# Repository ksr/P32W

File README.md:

# P32W

P32W: a 32-bit homebrew computer and its operating system. Discrete
74-series logic, GALs, SRAM and flash on **9U × 340 mm cards** with three
96-pin bus connectors, on a 10-slot backplane, with the ALU in an FPGA
module (a Tang Nano 20K in sockets: every part is through-hole). A custom
minimal load/store ISA with traps, interrupts and virtual memory, and
**P32W Unix**, a multi-user V6-style Unix in C, with a native C compiler,
assembler and linker, MicroPython, Lua, SQL, BASIC and networking.

The cards: **CPU**, **MMU / data**, **memory** (1–4 × 16 MiB), **disk**
(2 CompactFlash + 2 IDE), **I/O** (4 serial ports, timer, clock, 2 USB,
Ethernet and Wi-Fi), **video** (VGA text and graphics, PS/2 keyboard and
mouse) and **debug**. They meet on a synchronous system bus that carries
physical memory cycles; the CPU and the MMU / data card have a private
local link besides.

**Start here:** [docs/architecture.md](docs/architecture.md) (the machine,
the cards, the address map) and
[docs/programmers-guide.md](docs/programmers-guide.md) (how to program it).

- Design decisions: [docs/decisions.md](docs/decisions.md)
- The operating system: [docs/os-design.md](docs/os-design.md); using P32W Unix: [docs/unix.md](docs/unix.md)
- Working from a web browser, in a GitHub codespace: [.devcontainer/README.md](.devcontainer/README.md)
- The debugger, in a browser tab (the screen, the console, the code, the CPU's insides): [tools/p32dbg/README.md](tools/p32dbg/README.md)
- The backlog: [docs/backlog.md](docs/backlog.md)
- Instruction set: [docs/isa-v0.md](docs/isa-v0.md); traps, privilege,
  interrupts, timer and virtual memory (stages A–C):
  [docs/isa-system.md](docs/isa-system.md); every instruction in one table:
  [docs/instruction-reference.md](docs/instruction-reference.md) (generated)
- Microarchitecture: [docs/microarch.md](docs/microarch.md); the CPU card: [docs/cpu-card.md](docs/cpu-card.md); the MMU / data card: [docs/mmu-card.md](docs/mmu-card.md); the memory card: [docs/mem-card.md](docs/mem-card.md); the I/O card: [docs/io-card.md](docs/io-card.md); the disk card: [docs/disk-card.md](docs/disk-card.md); the video card: [docs/video-card-acrtc.md](docs/video-card-acrtc.md) (revision 2, an HD63484 ACRTC; revision 0, never built: [docs/video-card.md](docs/video-card.md)); the debug card: [docs/debug-card.md](docs/debug-card.md); each card's theory of operation beside it (`*-card-theory.md`); how it boots: [docs/boot.md](docs/boot.md); the kernel: [docs/kernel.md](docs/kernel.md); the filesystem: [docs/filesystem.md](docs/filesystem.md). `python3 tools/mkpdf.py` makes them PDF books (docs/pdf). The GALs' fuse files and how to program every chip (TL866II+ / T48): [hardware/gal/README.md](hardware/gal/README.md)
- ISA additions measured for the new datapath: [docs/isa-measurements.md](docs/isa-measurements.md)
- The backplane bus: [docs/bus.md](docs/bus.md) (generated by `generators/p32bus.py`); the backplane itself: [docs/backplane.md](docs/backplane.md); the power budget: [docs/power-budget.md](docs/power-budget.md); timing: [docs/timing.md](docs/timing.md)
- A bench tool for any system on 96-pin DIN 41612 connectors, the shorts tester: [docs/din96-tester.md](docs/din96-tester.md) (`hardware/din96-tester/`)
- The emulators: [docs/emulators.md](docs/emulators.md)

## The cards

Every card's netlist is designed and every board routed; none is ordered
yet. The first order is the backplane, the debug card, the memory card and
the DIN 96 tester ([docs/backlog.md](docs/backlog.md)). Each card's
schematic and placement PDFs, gerbers and renders are in
`hardware/<card>/kicad/`; the emulators model the cards
(`emulator/p32io.h`, `emulator/p32uemu.c`).

## Layout

| Directory | Contents |
|---|---|
| `microcode/` | `p32isa.py` — the opcode table, single source of truth for the ISA; `p32ucode.py` — the microcode generator |
| `generators/` | `p32bus.py` — the bus (`pinnet()`, `busnet()`); `p32net.py` — device library, netlist helpers, electrical checks; `p32cards.py` — the card list; `p32gal.py` — GAL equations, exhaustive checks, a logic minimiser; `p32sim.py` — netlist-level simulator; `p32schem.py` — schematic PDFs; `p32kicad_sch.py` — KiCad schematic projects; `p32kicad_pcb.py` + `build_board.sh` + `kicad_tools.py` — place, autoroute (Freerouting 2.5) and finish boards; `gen_footprints.py` — the project's footprints (`hardware/lib`); `gen_p32opc.py`, `gen_isaref.py` — the emulator header and the instruction reference |
| `assembler/` | `p32asm.py` — two-pass assembler, linker, archiver |
| `cc/` | `p32cc.py` — the C compiler |
| `emulator/` | `p32emu.c` — instruction-level reference emulator; `p32uemu.c` — microcode-level emulator, cross-checked against it; `p32io.h` — the devices, shared by both; tests in `test/` |
| `kernel/` | P32W Unix |
| `software/` | the boot ROM monitor, libc, the commands, MicroPython, Lua, SQL, the tests ([software/README.md](software/README.md)) |
| `fpga/alu/` | the ALU in Verilog, its testbench and vector generator |
| `hardware/` | one folder per card (`<card>/kicad/`: the KiCad project, schematic and placement PDFs, gerbers, renders, `pcb-check.ini`); `gal/` the GAL JEDEC files; `lib/` the project's KiCad footprints (generated) |
| `video/` | the video cards' font images |
| `tools/` | host tools: the PDF books (`mkpdf.py`), the debugger (`p32dbg`), the terminal, the file-system tool, profilers, Kermit |
| `website/` | the project website ([website/README.md](website/README.md)) |
| `docs/` | design documents |

## Build and test

```sh
cd generators && npm install      # once: elkjs, for the wired KiCad schematic sheets
cd emulator && make test          # everything: emulators, microcode, P32W Unix
```

Assemble and run a program:

```sh
python3 assembler/p32asm.py prog.asm -o prog.bin -l prog.lst
emulator/p32emu [-t] [-l N] [-d disk.img] prog.bin
```

Tools used: Python 3, a C compiler, KiCad 10 (schematics and boards),
Freerouting 2.5 on Java 25 (`~/freerouting/`), Icarus Verilog (the ALU test).

## Licence

P32W is © 2026 Ken Rother.

- **The designs and documents** — `hardware/`, `docs/`, the manual pages (`software/man/`) and the website text:
  [CC BY 4.0](LICENSE-CC-BY-4.0.md). Share and adapt them freely, with credit.
- **The software** — everything else written for P32W: the [MIT licence](LICENSE).
- **Third-party code** keeps its own licence and notices:
  - [MicroPython](software/micropython/) (MIT, `software/micropython/LICENSE`);
  - [Lua](software/lua/) (MIT, the notice at the end of `software/lua/lua.h`);
  - `software/libc/erf.c` and `gamma.c`, from musl via MicroPython (MIT, the notice in each file).

The network tests make their own TLS test certificate on first use (`emulator/test/net_peer.py`, `tls_cert()`);
it is for "localhost" only and not a secret, so it is not kept in the repository.

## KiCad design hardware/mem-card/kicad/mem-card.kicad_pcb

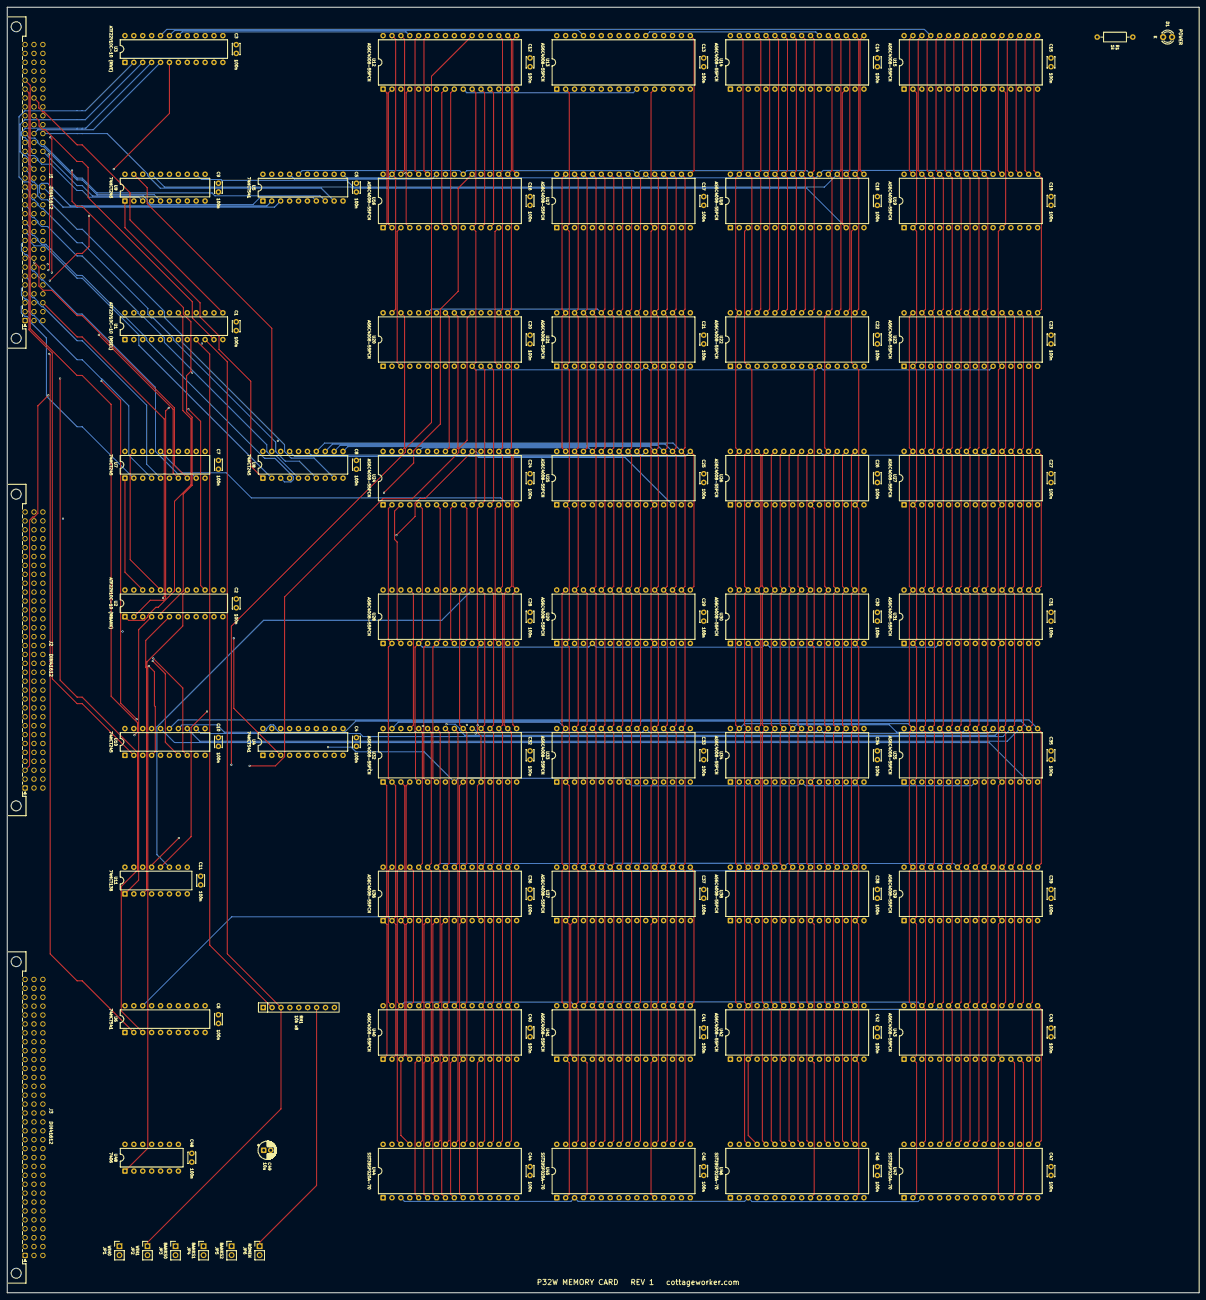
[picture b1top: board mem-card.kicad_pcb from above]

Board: 6 copper layers, 340.0 x 366.7 mm, 109 parts (0 on the bottom side), 151 nets.

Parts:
C1, C2, C3, C4, C5, C6, C7, C8, C9, C10, C11, C12, C13, C14, C15, C16, C17, C18, C19, C20, C21, C22, C23, C24, C25, C26, C27, C28, C29, C30, C31, C32, C33, C34, C35, C36, C37, C38, C39, C40, C41, C42, C43, C44, C45, C46, C47, C48: 100nF; C_Disc_D3.0mm_W2.0mm_P2.50mm
C49: 10uF 16V; CP_Radial_D5.0mm_P2.00mm
D1: LED 3mm green; LED_D3.0mm
J1, J2, J3: DIN 41612 96-pin male, right angle; DIN41612_C_3x32_Male_Horizontal_THT
JP1, JP2, JP3, JP4, JP5, JP6: jumper; PinHeader_1x02_P2.54mm_Vertical
R1: 1k; R_Axial_DIN0207_L6.3mm_D2.5mm_P10.16mm_Horizontal
RN1: 10k x 8 bussed; R_Array_SIP9
U1: ATF22V10C-10 (MSEL); DIP-24_W7.62mm
U2: ATF22V10C-10 (MBANK); DIP-24_W7.62mm
U3: ATF22V10C-10 (MWE); DIP-24_W7.62mm
U4, U5, U6: 74HCT541; DIP-20_W7.62mm
U7, U8, U9, U10: 74HCT245; DIP-20_W7.62mm
U11: 74HCT138; DIP-16_W7.62mm
U12, U13, U14, U15, U16, U17, U18, U19, U20, U21, U22, U23, U24, U25, U26, U27, U28, U29, U30, U31, U32, U33, U34, U35, U36, U37, U38, U39, U40, U41, U42, U43: AS6C4008-55PCN; DIP-32_W15.24mm
U44, U45, U46, U47: SST39SF020A-70; DIP-32_W15.24mm
U48: 7406; DIP-14_W7.62mm

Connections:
-ACK: J1.b28, U48.2
-MRD: J1.b24, U1.11
-MWR: J1.b26, U1.13
A2: J1.c7, U4.2
A3: J1.c8, U4.3
A4: J1.c9, U4.4
A5: J1.c10, U4.5
A6: J1.c11, U4.6
A7: J1.c12, U4.7
A8: J1.c13, U4.8
A9: J1.c14, U4.9
A10: J1.c15, U5.2
A11: J1.c16, U5.3
A12: J1.c17, U5.4
A13: J1.c18, U5.5
A14: J1.c19, U5.6
A15: J1.c20, U5.7
A16: J1.c21, U5.8
A17: J1.c22, U5.9
A18: J1.c23, U6.2
A19: J1.c24, U6.3
A20: J1.c25, U2.3, U6.4
A21: J1.c26, U2.4, U11.1
A22: J1.c27, U2.5, U11.2
A23: J1.c28, U2.6, U11.3
A24: J1.c29, U1.1
A25: J1.c30, U1.2
A26: J1.b4, U1.3
A27: J1.b6, U1.4
A28: J1.b8, U1.5
A29: J1.b10, U1.6
A30: J1.b12, U1.7
A31: J1.b14, U1.8
ACK: U2.17, U48.1
BANK0_N: U11.15, U12.22, U13.22, U14.22, U15.22
BANK1_N: U11.14, U16.22, U17.22, U18.22, U19.22
BANK2_N: U11.13, U20.22, U21.22, U22.22, U23.22
BANK3_N: U11.12, U24.22, U25.22, U26.22, U27.22
BANK4_N: U11.11, U28.22, U29.22, U30.22, U31.22
BANK5_N: U11.10, U32.22, U33.22, U34.22, U35.22
BANK6_N: U11.9, U36.22, U37.22, U38.22, U39.22
BANK7_N: U11.7, U40.22, U41.22, U42.22, U43.22
BANKS0: JP3.1, RN1.4, U2.7
BANKS1: JP4.1, RN1.5, U2.8
BANKS2: JP5.1, RN1.6, U2.9
BE0: J1.b16, U3.2
BE1: J1.b18, U3.3
BE2: J1.b20, U3.4
BE3: J1.b22, U3.5
CARDRD: U1.18, U2.1, U3.7
CARDWR: U1.19, U2.2
CLK: J2.a3, U3.6
D0: J1.a3, U7.2
D1: J1.a4, U7.3
D2: J1.a5, U7.4
D3: J1.a6, U7.5
D4: J1.a7, U7.6
D5: J1.a8, U7.7
D6: J1.a9, U7.8
D7: J1.a10, U7.9
D8: J1.a11, U8.2
D9: J1.a12, U8.3
D10: J1.a13, U8.4
D11: J1.a14, U8.5
D12: J1.a15, U8.6
D13: J1.a16, U8.7
D14: J1.a17, U8.8
D15: J1.a18, U8.9
D16: J1.a19, U9.2
D17: J1.a20, U9.3
D18: J1.a21, U9.4
D19: J1.a22, U9.5
D20: J1.a23, U9.6
D21: J1.a24, U9.7
D22: J1.a25, U9.8
D23: J1.a26, U9.9
D24: J1.a27, U10.2
D25: J1.a28, U10.3
D26: J1.a29, U10.4
D27: J1.a30, U10.5
D28: J1.c3, U10.6
D29: J1.c4, U10.7
D30: J1.c5, U10.8
D31: J1.c6, U10.9
DIRW: U2.22, U7.1, U8.1, U9.1, U10.1
GND: C1.2, C2.2, C3.2, C4.2, C5.2, C6.2, C7.2, C8.2, C9.2, C10.2, C11.2, C12.2, C13.2, C14.2, C15.2, C16.2, C17.2, C18.2, C19.2, C20.2, C21.2, C22.2, C23.2, C24.2, C25.2, C26.2, C27.2, C28.2, C29.2, C30.2, C31.2, C32.2, C33.2, C34.2, C35.2, C36.2, C37.2, C38.2, C39.2, C40.2, C41.2, C42.2, C43.2, C44.2, C45.2, C46.2, C47.2, C48.2, C49.2, D1.1, J1.a31, J1.a32, J1.b3, J1.b5, J1.b7, J1.b9, J1.b11, J1.b13, J1.b15, J1.b17, J1.b19, J1.b21, J1.b23, J1.b25, J1.b27, J1.b29, J1.b31, J1.b32, J1.c31, J1.c32, J2.a31, J2.a32, J2.b3, J2.b5, J2.b7, J2.b9, J2.b11, J2.b13, J2.b15, J2.b17, J2.b19, J2.b21, J2.b23, J2.b25, J2.b27, J2.b29, J2.b31, J2.b32, J2.c31, J2.c32, J3.a31, J3.a32, J3.b3, J3.b5, J3.b7, J3.b9, J3.b11, J3.b13, J3.b15, J3.b17, J3.b19, J3.b21, J3.b23, J3.b25, J3.b27, J3.b29, J3.b31, J3.b32, J3.c31, J3.c32, JP1.2, JP2.2, JP3.2, JP4.2, JP5.2, JP6.2, U1.12, U2.12, U3.12, U4.1, U4.10, U4.19, U5.1, U5.10, U5.19, U6.1, U6.5, U6.6, U6.7, U6.8, U6.9, U6.10, U6.19, U7.10, U8.10, U9.10, U10.10, U11.5, U11.8, U12.16, U13.16, U14.16, U15.16, U16.16, U17.16, U18.16, U19.16, U20.16, U21.16, U22.16, U23.16, U24.16, U25.16, U26.16, U27.16, U28.16, U29.16, U30.16, U31.16, U32.16, U33.16, U34.16, U35.16, U36.16, U37.16, U38.16, U39.16, U40.16, U41.16, U42.16, U43.16, U44.16, U45.16, U46.16, U47.16, U48.3, U48.5, U48.7, U48.9, U48.11, U48.13
MA0: U4.18, U12.12, U13.12, U14.12, U15.12, U16.12, U17.12, U18.12, U19.12, U20.12, U21.12, U22.12, U23.12, U24.12, U25.12, U26.12, U27.12, U28.12, U29.12, U30.12, U31.12, U32.12, U33.12, U34.12, U35.12, U36.12, U37.12, U38.12, U39.12, U40.12, U41.12, U42.12, U43.12, U44.12, U45.12, U46.12, U47.12
MA1: U4.17, U12.11, U13.11, U14.11, U15.11, U16.11, U17.11, U18.11, U19.11, U20.11, U21.11, U22.11, U23.11, U24.11, U25.11, U26.11, U27.11, U28.11, U29.11, U30.11, U31.11, U32.11, U33.11, U34.11, U35.11, U36.11, U37.11, U38.11, U39.11, U40.11, U41.11, U42.11, U43.11, U44.11, U45.11, U46.11, U47.11
MA2: U4.16, U12.10, U13.10, U14.10, U15.10, U16.10, U17.10, U18.10, U19.10, U20.10, U21.10, U22.10, U23.10, U24.10, U25.10, U26.10, U27.10, U28.10, U29.10, U30.10, U31.10, U32.10, U33.10, U34.10, U35.10, U36.10, U37.10, U38.10, U39.10, U40.10, U41.10, U42.10, U43.10, U44.10, U45.10, U46.10, U47.10
MA3: U4.15, U12.9, U13.9, U14.9, U15.9, U16.9, U17.9, U18.9, U19.9, U20.9, U21.9, U22.9, U23.9, U24.9, U25.9, U26.9, U27.9, U28.9, U29.9, U30.9, U31.9, U32.9, U33.9, U34.9, U35.9, U36.9, U37.9, U38.9, U39.9, U40.9, U41.9, U42.9, U43.9, U44.9, U45.9, U46.9, U47.9
MA4: U4.14, U12.8, U13.8, U14.8, U15.8, U16.8, U17.8, U18.8, U19.8, U20.8, U21.8, U22.8, U23.8, U24.8, U25.8, U26.8, U27.8, U28.8, U29.8, U30.8, U31.8, U32.8, U33.8, U34.8, U35.8, U36.8, U37.8, U38.8, U39.8, U40.8, U41.8, U42.8, U43.8, U44.8, U45.8, U46.8, U47.8
MA5: U4.13, U12.7, U13.7, U14.7, U15.7, U16.7, U17.7, U18.7, U19.7, U20.7, U21.7, U22.7, U23.7, U24.7, U25.7, U26.7, U27.7, U28.7, U29.7, U30.7, U31.7, U32.7, U33.7, U34.7, U35.7, U36.7, U37.7, U38.7, U39.7, U40.7, U41.7, U42.7, U43.7, U44.7, U45.7, U46.7, U47.7
MA6: U4.12, U12.6, U13.6, U14.6, U15.6, U16.6, U17.6, U18.6, U19.6, U20.6, U21.6, U22.6, U23.6, U24.6, U25.6, U26.6, U27.6, U28.6, U29.6, U30.6, U31.6, U32.6, U33.6, U34.6, U35.6, U36.6, U37.6, U38.6, U39.6, U40.6, U41.6, U42.6, U43.6, U44.6, U45.6, U46.6, U47.6
MA7: U4.11, U12.5, U13.5, U14.5, U15.5, U16.5, U17.5, U18.5, U19.5, U20.5, U21.5, U22.5, U23.5, U24.5, U25.5, U26.5, U27.5, U28.5, U29.5, U30.5, U31.5, U32.5, U33.5, U34.5, U35.5, U36.5, U37.5, U38.5, U39.5, U40.5, U41.5, U42.5, U43.5, U44.5, U45.5, U46.5, U47.5
MA8: U5.18, U12.27, U13.27, U14.27, U15.27, U16.27, U17.27, U18.27, U19.27, U20.27, U21.27, U22.27, U23.27, U24.27, U25.27, U26.27, U27.27, U28.27, U29.27, U30.27, U31.27, U32.27, U33.27, U34.27, U35.27, U36.27, U37.27, U38.27, U39.27, U40.27, U41.27, U42.27, U43.27, U44.27, U45.27, U46.27, U47.27
MA9: U5.17, U12.26, U13.26, U14.26, U15.26, U16.26, U17.26, U18.26, U19.26, U20.26, U21.26, U22.26, U23.26, U24.26, U25.26, U26.26, U27.26, U28.26, U29.26, U30.26, U31.26, U32.26, U33.26, U34.26, U35.26, U36.26, U37.26, U38.26, U39.26, U40.26, U41.26, U42.26, U43.26, U44.26, U45.26, U46.26, U47.26
MA10: U5.16, U12.23, U13.23, U14.23, U15.23, U16.23, U17.23, U18.23, U19.23, U20.23, U21.23, U22.23, U23.23, U24.23, U25.23, U26.23, U27.23, U28.23, U29.23, U30.23, U31.23, U32.23, U33.23, U34.23, U35.23, U36.23, U37.23, U38.23, U39.23, U40.23, U41.23, U42.23, U43.23, U44.23, U45.23, U46.23, U47.23
MA11: U5.15, U12.25, U13.25, U14.25, U15.25, U16.25, U17.25, U18.25, U19.25, U20.25, U21.25, U22.25, U23.25, U24.25, U25.25, U26.25, U27.25, U28.25, U29.25, U30.25, U31.25, U32.25, U33.25, U34.25, U35.25, U36.25, U37.25, U38.25, U39.25, U40.25, U41.25, U42.25, U43.25, U44.25, U45.25, U46.25, U47.25
MA12: U5.14, U12.4, U13.4, U14.4, U15.4, U16.4, U17.4, U18.4, U19.4, U20.4, U21.4, U22.4, U23.4, U24.4, U25.4, U26.4, U27.4, U28.4, U29.4, U30.4, U31.4, U32.4, U33.4, U34.4, U35.4, U36.4, U37.4, U38.4, U39.4, U40.4, U41.4, U42.4, U43.4, U44.4, U45.4, U46.4, U47.4
MA13: U5.13, U12.28, U13.28, U14.28, U15.28, U16.28, U17.28, U18.28, U19.28, U20.28, U21.28, U22.28, U23.28, U24.28, U25.28, U26.28, U27.28, U28.28, U29.28, U30.28, U31.28, U32.28, U33.28, U34.28, U35.28, U36.28, U37.28, U38.28, U39.28, U40.28, U41.28, U42.28, U43.28, U44.28, U45.28, U46.28, U47.28
MA14: U5.12, U12.3, U13.3, U14.3, U15.3, U16.3, U17.3, U18.3, U19.3, U20.3, U21.3, U22.3, U23.3, U24.3, U25.3, U26.3, U27.3, U28.3, U29.3, U30.3, U31.3, U32.3, U33.3, U34.3, U35.3, U36.3, U37.3, U38.3, U39.3, U40.3, U41.3, U42.3, U43.3, U44.29, U45.29, U46.29, U47.29
MA15: U5.11, U12.31, U13.31, U14.31, U15.31, U16.31, U17.31, U18.31, U19.31, U20.31, U21.31, U22.31, U23.31, U24.31, U25.31, U26.31, U27.31, U28.31, U29.31, U30.31, U31.31, U32.31, U33.31, U34.31, U35.31, U36.31, U37.31, U38.31, U39.31, U40.31, U41.31, U42.31, U43.31, U44.3, U45.3, U46.3, U47.3
MA16: U6.18, U12.2, U13.2, U14.2, U15.2, U16.2, U17.2, U18.2, U19.2, U20.2, U21.2, U22.2, U23.2, U24.2, U25.2, U26.2, U27.2, U28.2, U29.2, U30.2, U31.2, U32.2, U33.2, U34.2, U35.2, U36.2, U37.2, U38.2, U39.2, U40.2, U41.2, U42.2, U43.2, U44.2, U45.2, U46.2, U47.2
MA17: U6.17, U12.30, U13.30, U14.30, U15.30, U16.30, U17.30, U18.30, U19.30, U20.30, U21.30, U22.30, U23.30, U24.30, U25.30, U26.30, U27.30, U28.30, U29.30, U30.30, U31.30, U32.30, U33.30, U34.30, U35.30, U36.30, U37.30, U38.30, U39.30, U40.30, U41.30, U42.30, U43.30, U44.30, U45.30, U46.30, U47.30
MA18: U6.16, U12.1, U13.1, U14.1, U15.1, U16.1, U17.1, U18.1, U19.1, U20.1, U21.1, U22.1, U23.1, U24.1, U25.1, U26.1, U27.1, U28.1, U29.1, U30.1, U31.1, U32.1, U33.1, U34.1, U35.1, U36.1, U37.1, U38.1, U39.1, U40.1, U41.1, U42.1, U43.1
MD0: U7.18, U12.13, U16.13, U20.13, U24.13, U28.13, U32.13, U36.13, U40.13, U44.13
MD1: U7.17, U12.14, U16.14, U20.14, U24.14, U28.14, U32.14, U36.14, U40.14, U44.14
MD2: U7.16, U12.15, U16.15, U20.15, U24.15, U28.15, U32.15, U36.15, U40.15, U44.15
MD3: U7.15, U12.17, U16.17, U20.17, U24.17, U28.17, U32.17, U36.17, U40.17, U44.17
MD4: U7.14, U12.18, U16.18, U20.18, U24.18, U28.18, U32.18, U36.18, U40.18, U44.18
MD5: U7.13, U12.19, U16.19, U20.19, U24.19, U28.19, U32.19, U36.19, U40.19, U44.19
MD6: U7.12, U12.20, U16.20, U20.20, U24.20, U28.20, U32.20, U36.20, U40.20, U44.20
MD7: U7.11, U12.21, U16.21, U20.21, U24.21, U28.21, U32.21, U36.21, U40.21, U44.21
MD8: U8.18, U13.13, U17.13, U21.13, U25.13, U29.13, U33.13, U37.13, U41.13, U45.13
MD9: U8.17, U13.14, U17.14, U21.14, U25.14, U29.14, U33.14, U37.14, U41.14, U45.14
MD10: U8.16, U13.15, U17.15, U21.15, U25.15, U29.15, U33.15, U37.15, U41.15, U45.15
MD11: U8.15, U13.17, U17.17, U21.17, U25.17, U29.17, U33.17, U37.17, U41.17, U45.17
MD12: U8.14, U13.18, U17.18, U21.18, U25.18, U29.18, U33.18, U37.18, U41.18, U45.18
MD13: U8.13, U13.19, U17.19, U21.19, U25.19, U29.19, U33.19, U37.19, U41.19, U45.19
MD14: U8.12, U13.20, U17.20, U21.20, U25.20, U29.20, U33.20, U37.20, U41.20, U45.20
MD15: U8.11, U13.21, U17.21, U21.21, U25.21, U29.21, U33.21, U37.21, U41.21, U45.21
MD16: U9.18, U14.13, U18.13, U22.13, U26.13, U30.13, U34.13, U38.13, U42.13, U46.13
MD17: U9.17, U14.14, U18.14, U22.14, U26.14, U30.14, U34.14, U38.14, U42.14, U46.14
MD18: U9.16, U14.15, U18.15, U22.15, U26.15, U30.15, U34.15, U38.15, U42.15, U46.15
MD19: U9.15, U14.17, U18.17, U22.17, U26.17, U30.17, U34.17, U38.17, U42.17, U46.17
MD20: U9.14, U14.18, U18.18, U22.18, U26.18, U30.18, U34.18, U38.18, U42.18, U46.18
MD21: U9.13, U14.19, U18.19, U22.19, U26.19, U30.19, U34.19, U38.19, U42.19, U46.19
MD22: U9.12, U14.20, U18.20, U22.20, U26.20, U30.20, U34.20, U38.20, U42.20, U46.20
MD23: U9.11, U14.21, U18.21, U22.21, U26.21, U30.21, U34.21, U38.21, U42.21, U46.21
MD24: U10.18, U15.13, U19.13, U23.13, U27.13, U31.13, U35.13, U39.13, U43.13, U47.13
MD25: U10.17, U15.14, U19.14, U23.14, U27.14, U31.14, U35.14, U39.14, U43.14, U47.14
MD26: U10.16, U15.15, U19.15, U23.15, U27.15, U31.15, U35.15, U39.15, U43.15, U47.15
MD27: U10.15, U15.17, U19.17, U23.17, U27.17, U31.17, U35.17, U39.17, U43.17, U47.17
MD28: U10.14, U15.18, U19.18, U23.18, U27.18, U31.18, U35.18, U39.18, U43.18, U47.18
MD29: U10.13, U15.19, U19.19, U23.19, U27.19, U31.19, U35.19, U39.19, U43.19, U47.19
MD30: U10.12, U15.20, U19.20, U23.20, U27.20, U31.20, U35.20, U39.20, U43.20, U47.20
MD31: U10.11, U15.21, U19.21, U23.21, U27.21, U31.21, U35.21, U39.21, U43.21, U47.21
PWRLED_A: D1.2, R1.2
RAMENN: U2.19, U11.4
RAMWR: U2.15, U3.1
RDOEN: U3.16, U12.24, U13.24, U14.24, U15.24, U16.24, U17.24, U18.24, U19.24, U20.24, U21.24, U22.24, U23.24, U24.24, U25.24, U26.24, U27.24, U28.24, U29.24, U30.24, U31.24, U32.24, U33.24, U34.24, U35.24, U36.24, U37.24, U38.24, U39.24, U40.24, U41.24, U42.24, U43.24, U44.24, U45.24, U46.24, U47.24
ROMCSN: U2.16, U44.22, U45.22, U46.22, U47.22
ROMEN: JP6.1, RN1.7, U2.10
VCC: C1.1, C2.1, C3.1, C4.1, C5.1, C6.1, C7.1, C8.1, C9.1, C10.1, C11.1, C12.1, C13.1, C14.1, C15.1, C16.1, C17.1, C18.1, C19.1, C20.1, C21.1, C22.1, C23.1, C24.1, C25.1, C26.1, C27.1, C28.1, C29.1, C30.1, C31.1, C32.1, C33.1, C34.1, C35.1, C36.1, C37.1, C38.1, C39.1, C40.1, C41.1, C42.1, C43.1, C44.1, C45.1, C46.1, C47.1, C48.1, C49.1, J1.a1, J1.a2, J1.b1, J1.b2, J1.c1, J1.c2, J2.a1, J2.a2, J2.b1, J2.b2, J2.b4, J2.b6, J2.b8, J2.b10, J2.b12, J2.b14, J2.b16, J2.b18, J2.b20, J2.b22, J2.b24, J2.b26, J2.b28, J2.b30, J2.c1, J2.c2, J3.a1, J3.a2, J3.b1, J3.b2, J3.c1, J3.c2, R1.1, RN1.1, U1.24, U2.24, U3.24, U4.20, U5.20, U6.20, U7.20, U8.20, U9.20, U10.20, U11.6, U11.16, U12.32, U13.32, U14.32, U15.32, U16.32, U17.32, U18.32, U19.32, U20.32, U21.32, U22.32, U23.32, U24.32, U25.32, U26.32, U27.32, U28.32, U29.32, U30.32, U31.32, U32.32, U33.32, U34.32, U35.32, U36.32, U37.32, U38.32, U39.32, U40.32, U41.32, U42.32, U43.32, U44.31, U44.32, U45.31, U45.32, U46.31, U46.32, U47.31, U47.32, U48.14
WE0N: U3.18, U12.29, U16.29, U20.29, U24.29, U28.29, U32.29, U36.29, U40.29
WE1N: U3.19, U13.29, U17.29, U21.29, U25.29, U29.29, U33.29, U37.29, U41.29
WE2N: U3.17, U14.29, U18.29, U22.29, U26.29, U30.29, U34.29, U38.29, U42.29
WE3N: U3.20, U15.29, U19.29, U23.29, U27.29, U31.29, U35.29, U39.29, U43.29
WIN0: JP1.1, RN1.2, U1.9
WIN1: JP2.1, RN1.3, U1.10
XOEN: U2.20, U7.19, U8.19, U9.19, U10.19

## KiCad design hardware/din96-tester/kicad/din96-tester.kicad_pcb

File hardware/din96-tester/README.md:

# The DIN 96 shorts tester

A bench tool for any system on 96-pin DIN 41612 connectors (P32W, YACC1): plugged onto one connector of a board
that has nothing on it yet but its connectors, it finds every pin joined to another. An Arduino Nano, six
MCP23S17 port expanders, a TEST button, an eight-lever TYPE switch, and three LEDs: POWER (yellow), PASS (green),
FAIL (red). What it is, how to use it and how it works:
[docs/din96-tester.md](../../docs/din96-tester.md) (decisions D129, and D130: its check before the order).

- `kicad/`: the schematic, the board and its order files, made by `generators/card_din96.py` (the netlist) and
  `generators/p32din96.py` (the board): `sh generators/build_schematics.sh din96-tester`, then
  `sh generators/build_board.sh din96-tester`. Generators are canon: do not edit the board by hand.
- `firmware/din96_tester/`: the Arduino sketch. `profiles.h` is written by `python3 generators/card_din96.py
  --firmware`; the other two files are edited by hand. `make test` (in `emulator/`) runs its logic on made-up
  boards (`emulator/test/din96_test.c`) and the sketch itself against a model of this board
  (`emulator/test/din96_sim.cc`).
- `pins/`: a pin table a system (`CONNECTOR PIN SIGNAL`), which the connector types are made from. `p32w.txt` is
  written from P32W's bus definition; `yacc1.txt` is a copy of what YACC1-D's `tools/bus_pins.py` prints.

Another system: put its pin table in `pins/`, add its connector to `TYPES` in `generators/card_din96.py`, run
`--firmware`, and load the sketch again.

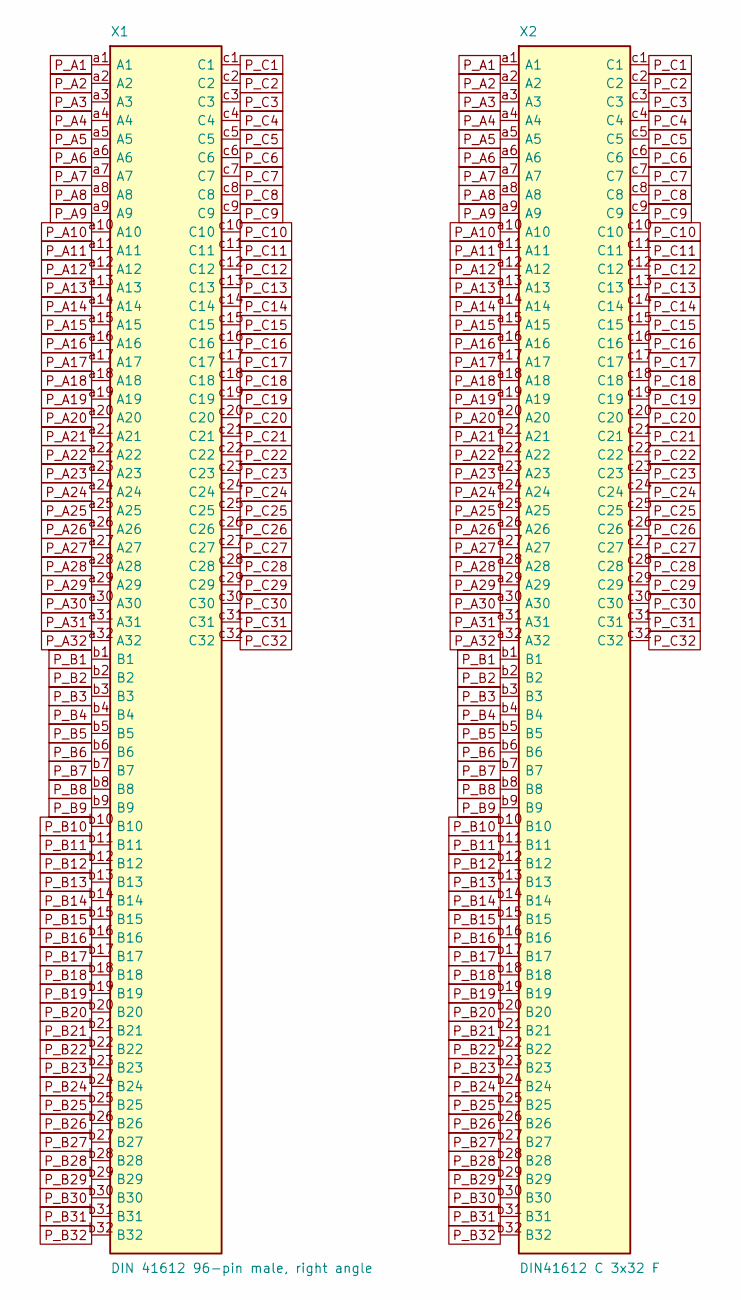
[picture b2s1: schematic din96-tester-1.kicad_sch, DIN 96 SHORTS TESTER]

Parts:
X1: DIN 41612 96-pin male, right angle; DIN41612_C_3x32_Male_Horizontal_THT
X2: DIN41612 C 3x32 F; DIN41612_C_3x32_Female_Vertical_THT

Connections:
P_A1: X1.a1 (A1), X2.a1 (A1); also elsewhere on the board
P_A2: X1.a2 (A2), X2.a2 (A2); also elsewhere on the board
P_A3: X1.a3 (A3), X2.a3 (A3); also elsewhere on the board
P_A4: X1.a4 (A4), X2.a4 (A4); also elsewhere on the board
P_A5: X1.a5 (A5), X2.a5 (A5); also elsewhere on the board
P_A6: X1.a6 (A6), X2.a6 (A6); also elsewhere on the board
P_A7: X1.a7 (A7), X2.a7 (A7); also elsewhere on the board
P_A8: X1.a8 (A8), X2.a8 (A8); also elsewhere on the board
P_A9: X1.a9 (A9), X2.a9 (A9); also elsewhere on the board
P_A10: X1.a10 (A10), X2.a10 (A10); also elsewhere on the board
P_A11: X1.a11 (A11), X2.a11 (A11); also elsewhere on the board
P_A12: X1.a12 (A12), X2.a12 (A12); also elsewhere on the board
P_A13: X1.a13 (A13), X2.a13 (A13); also elsewhere on the board
P_A14: X1.a14 (A14), X2.a14 (A14); also elsewhere on the board
P_A15: X1.a15 (A15), X2.a15 (A15); also elsewhere on the board
P_A16: X1.a16 (A16), X2.a16 (A16); also elsewhere on the board
P_A17: X1.a17 (A17), X2.a17 (A17); also elsewhere on the board
P_A18: X1.a18 (A18), X2.a18 (A18); also elsewhere on the board
P_A19: X1.a19 (A19), X2.a19 (A19); also elsewhere on the board
P_A20: X1.a20 (A20), X2.a20 (A20); also elsewhere on the board
P_A21: X1.a21 (A21), X2.a21 (A21); also elsewhere on the board
P_A22: X1.a22 (A22), X2.a22 (A22); also elsewhere on the board
P_A23: X1.a23 (A23), X2.a23 (A23); also elsewhere on the board
P_A24: X1.a24 (A24), X2.a24 (A24); also elsewhere on the board
P_A25: X1.a25 (A25), X2.a25 (A25); also elsewhere on the board
P_A26: X1.a26 (A26), X2.a26 (A26); also elsewhere on the board
P_A27: X1.a27 (A27), X2.a27 (A27); also elsewhere on the board
P_A28: X1.a28 (A28), X2.a28 (A28); also elsewhere on the board
P_A29: X1.a29 (A29), X2.a29 (A29); also elsewhere on the board
P_A30: X1.a30 (A30), X2.a30 (A30); also elsewhere on the board
P_A31: X1.a31 (A31), X2.a31 (A31); also elsewhere on the board
P_A32: X1.a32 (A32), X2.a32 (A32); also elsewhere on the board
P_B1: X1.b1 (B1), X2.b1 (B1); also elsewhere on the board
P_B2: X1.b2 (B2), X2.b2 (B2); also elsewhere on the board
P_B3: X1.b3 (B3), X2.b3 (B3); also elsewhere on the board
P_B4: X1.b4 (B4), X2.b4 (B4); also elsewhere on the board
P_B5: X1.b5 (B5), X2.b5 (B5); also elsewhere on the board
P_B6: X1.b6 (B6), X2.b6 (B6); also elsewhere on the board
P_B7: X1.b7 (B7), X2.b7 (B7); also elsewhere on the board
P_B8: X1.b8 (B8), X2.b8 (B8); also elsewhere on the board
P_B9: X1.b9 (B9), X2.b9 (B9); also elsewhere on the board
P_B10: X1.b10 (B10), X2.b10 (B10); also elsewhere on the board
P_B11: X1.b11 (B11), X2.b11 (B11); also elsewhere on the board
P_B12: X1.b12 (B12), X2.b12 (B12); also elsewhere on the board
P_B13: X1.b13 (B13), X2.b13 (B13); also elsewhere on the board
P_B14: X1.b14 (B14), X2.b14 (B14); also elsewhere on the board
P_B15: X1.b15 (B15), X2.b15 (B15); also elsewhere on the board
P_B16: X1.b16 (B16), X2.b16 (B16); also elsewhere on the board
P_B17: X1.b17 (B17), X2.b17 (B17); also elsewhere on the board
P_B18: X1.b18 (B18), X2.b18 (B18); also elsewhere on the board
P_B19: X1.b19 (B19), X2.b19 (B19); also elsewhere on the board
P_B20: X1.b20 (B20), X2.b20 (B20); also elsewhere on the board
P_B21: X1.b21 (B21), X2.b21 (B21); also elsewhere on the board
P_B22: X1.b22 (B22), X2.b22 (B22); also elsewhere on the board
P_B23: X1.b23 (B23), X2.b23 (B23); also elsewhere on the board
P_B24: X1.b24 (B24), X2.b24 (B24); also elsewhere on the board
P_B25: X1.b25 (B25), X2.b25 (B25); also elsewhere on the board
P_B26: X1.b26 (B26), X2.b26 (B26); also elsewhere on the board
P_B27: X1.b27 (B27), X2.b27 (B27); also elsewhere on the board
P_B28: X1.b28 (B28), X2.b28 (B28); also elsewhere on the board
P_B29: X1.b29 (B29), X2.b29 (B29); also elsewhere on the board
P_B30: X1.b30 (B30), X2.b30 (B30); also elsewhere on the board
P_B31: X1.b31 (B31), X2.b31 (B31); also elsewhere on the board
P_B32: X1.b32 (B32), X2.b32 (B32); also elsewhere on the board
P_C1: X1.c1 (C1), X2.c1 (C1); also elsewhere on the board
P_C2: X1.c2 (C2), X2.c2 (C2); also elsewhere on the board
P_C3: X1.c3 (C3), X2.c3 (C3); also elsewhere on the board
P_C4: X1.c4 (C4), X2.c4 (C4); also elsewhere on the board
P_C5: X1.c5 (C5), X2.c5 (C5); also elsewhere on the board
P_C6: X1.c6 (C6), X2.c6 (C6); also elsewhere on the board
P_C7: X1.c7 (C7), X2.c7 (C7); also elsewhere on the board
P_C8: X1.c8 (C8), X2.c8 (C8); also elsewhere on the board
P_C9: X1.c9 (C9), X2.c9 (C9); also elsewhere on the board
P_C10: X1.c10 (C10), X2.c10 (C10); also elsewhere on the board
P_C11: X1.c11 (C11), X2.c11 (C11); also elsewhere on the board
P_C12: X1.c12 (C12), X2.c12 (C12); also elsewhere on the board
P_C13: X1.c13 (C13), X2.c13 (C13); also elsewhere on the board
P_C14: X1.c14 (C14), X2.c14 (C14); also elsewhere on the board
P_C15: X1.c15 (C15), X2.c15 (C15); also elsewhere on the board
P_C16: X1.c16 (C16), X2.c16 (C16); also elsewhere on the board
P_C17: X1.c17 (C17), X2.c17 (C17); also elsewhere on the board
P_C18: X1.c18 (C18), X2.c18 (C18); also elsewhere on the board
P_C19: X1.c19 (C19), X2.c19 (C19); also elsewhere on the board
P_C20: X1.c20 (C20), X2.c20 (C20); also elsewhere on the board
P_C21: X1.c21 (C21), X2.c21 (C21); also elsewhere on the board
P_C22: X1.c22 (C22), X2.c22 (C22); also elsewhere on the board
P_C23: X1.c23 (C23), X2.c23 (C23); also elsewhere on the board
P_C24: X1.c24 (C24), X2.c24 (C24); also elsewhere on the board
P_C25: X1.c25 (C25), X2.c25 (C25); also elsewhere on the board
P_C26: X1.c26 (C26), X2.c26 (C26); also elsewhere on the board
P_C27: X1.c27 (C27), X2.c27 (C27); also elsewhere on the board
P_C28: X1.c28 (C28), X2.c28 (C28); also elsewhere on the board
P_C29: X1.c29 (C29), X2.c29 (C29); also elsewhere on the board
P_C30: X1.c30 (C30), X2.c30 (C30); also elsewhere on the board
P_C31: X1.c31 (C31), X2.c31 (C31); also elsewhere on the board
P_C32: X1.c32 (C32), X2.c32 (C32); also elsewhere on the board

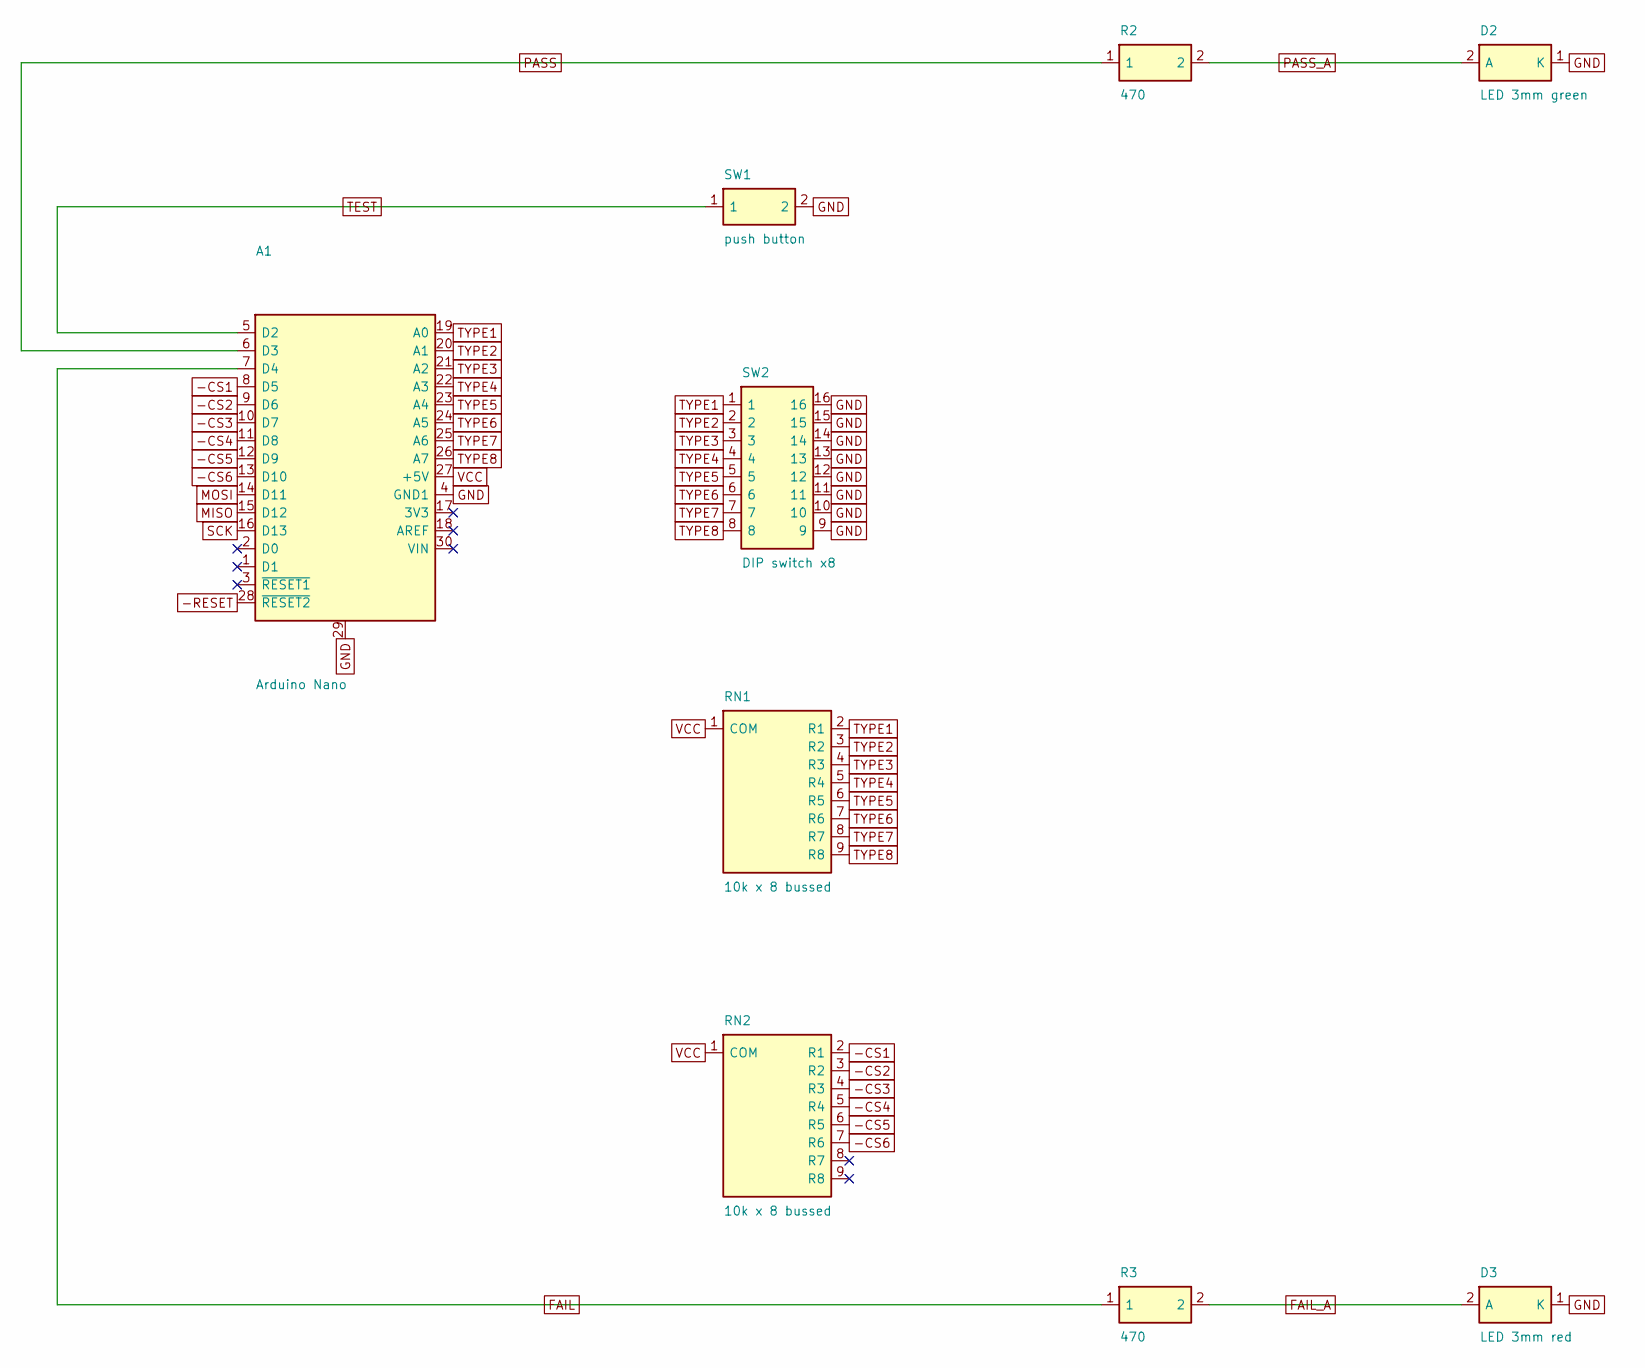
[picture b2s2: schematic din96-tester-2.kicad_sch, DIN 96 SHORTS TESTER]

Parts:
A1: Arduino Nano; Arduino_Nano
D2: LED 3mm green; LED_D3.0mm
D3: LED 3mm red; LED_D3.0mm
R2, R3: 470; R_Axial_DIN0207_L6.3mm_D2.5mm_P10.16mm_Horizontal
RN1, RN2: 10k x 8 bussed; R_Array_SIP9
SW1: push button; SW_PUSH_6mm
SW2: DIP switch x8; SW_DIP_SPSTx08_Slide_9.78x22.5mm_W7.62mm_P2.54mm

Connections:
-CS1: A1.8 (D5), RN2.2 (R1); also elsewhere on the board
-CS2: A1.9 (D6), RN2.3 (R2); also elsewhere on the board
-CS3: A1.10 (D7), RN2.4 (R3); also elsewhere on the board
-CS4: A1.11 (D8), RN2.5 (R4); also elsewhere on the board
-CS5: A1.12 (D9), RN2.6 (R5); also elsewhere on the board
-CS6: A1.13 (D10), RN2.7 (R6); also elsewhere on the board
-RESET: A1.28 (~RESET2); also elsewhere on the board
FAIL: A1.7 (D4), R3.1
FAIL_A: D3.2 (A), R3.2
GND: A1.4 (GND1), A1.29, D2.1 (K), D3.1 (K), SW1.2, SW2.9, SW2.10, SW2.11, SW2.12, SW2.13, SW2.14, SW2.15, SW2.16; also elsewhere on the board
MISO: A1.15 (D12); also elsewhere on the board
MOSI: A1.14 (D11); also elsewhere on the board
PASS: A1.6 (D3), R2.1
PASS_A: D2.2 (A), R2.2
SCK: A1.16 (D13); also elsewhere on the board
TEST: A1.5 (D2), SW1.1
TYPE1: A1.19 (A0), RN1.2 (R1), SW2.1
TYPE2: A1.20 (A1), RN1.3 (R2), SW2.2
TYPE3: A1.21 (A2), RN1.4 (R3), SW2.3
TYPE4: A1.22 (A3), RN1.5 (R4), SW2.4
TYPE5: A1.23 (A4), RN1.6 (R5), SW2.5
TYPE6: A1.24 (A5), RN1.7 (R6), SW2.6
TYPE7: A1.25 (A6), RN1.8 (R7), SW2.7
TYPE8: A1.26 (A7), RN1.9 (R8), SW2.8
VCC: A1.27 (+5V), RN1.1 (COM), RN2.1 (COM); also elsewhere on the board

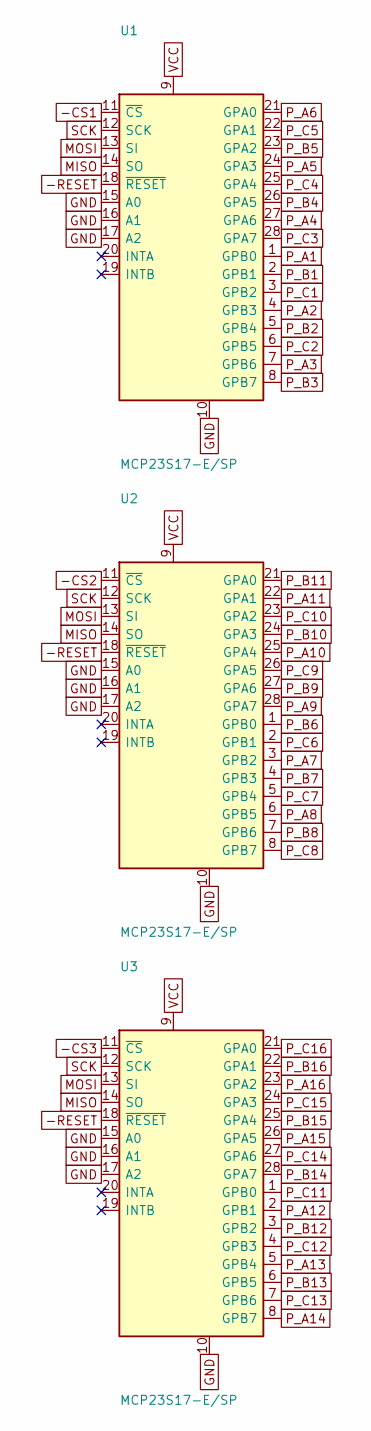
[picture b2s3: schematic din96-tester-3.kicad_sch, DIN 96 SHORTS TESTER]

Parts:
U1, U2, U3: MCP23S17-E/SP; DIP-28_W7.62mm

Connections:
-CS1: U1.11 (~CS); also elsewhere on the board
-CS2: U2.11 (~CS); also elsewhere on the board
-CS3: U3.11 (~CS); also elsewhere on the board
-RESET: U1.18 (~RESET), U2.18 (~RESET), U3.18 (~RESET); also elsewhere on the board
GND: U1.10, U1.15 (A0), U1.16 (A1), U1.17 (A2), U2.10, U2.15 (A0), U2.16 (A1), U2.17 (A2), U3.10, U3.15 (A0), U3.16 (A1), U3.17 (A2); also elsewhere on the board
MISO: U1.14 (SO), U2.14 (SO), U3.14 (SO); also elsewhere on the board
MOSI: U1.13 (SI), U2.13 (SI), U3.13 (SI); also elsewhere on the board
P_A1: U1.1 (GPB0); also elsewhere on the board
P_A2: U1.4 (GPB3); also elsewhere on the board
P_A3: U1.7 (GPB6); also elsewhere on the board
P_A4: U1.27 (GPA6); also elsewhere on the board
P_A5: U1.24 (GPA3); also elsewhere on the board
P_A6: U1.21 (GPA0); also elsewhere on the board
P_A7: U2.3 (GPB2); also elsewhere on the board
P_A8: U2.6 (GPB5); also elsewhere on the board
P_A9: U2.28 (GPA7); also elsewhere on the board
P_A10: U2.25 (GPA4); also elsewhere on the board
P_A11: U2.22 (GPA1); also elsewhere on the board
P_A12: U3.2 (GPB1); also elsewhere on the board
P_A13: U3.5 (GPB4); also elsewhere on the board
P_A14: U3.8 (GPB7); also elsewhere on the board
P_A15: U3.26 (GPA5); also elsewhere on the board
P_A16: U3.23 (GPA2); also elsewhere on the board
P_B1: U1.2 (GPB1); also elsewhere on the board
P_B2: U1.5 (GPB4); also elsewhere on the board
P_B3: U1.8 (GPB7); also elsewhere on the board
P_B4: U1.26 (GPA5); also elsewhere on the board
P_B5: U1.23 (GPA2); also elsewhere on the board
P_B6: U2.1 (GPB0); also elsewhere on the board
P_B7: U2.4 (GPB3); also elsewhere on the board
P_B8: U2.7 (GPB6); also elsewhere on the board
P_B9: U2.27 (GPA6); also elsewhere on the board
P_B10: U2.24 (GPA3); also elsewhere on the board
P_B11: U2.21 (GPA0); also elsewhere on the board
P_B12: U3.3 (GPB2); also elsewhere on the board
P_B13: U3.6 (GPB5); also elsewhere on the board
P_B14: U3.28 (GPA7); also elsewhere on the board
P_B15: U3.25 (GPA4); also elsewhere on the board
P_B16: U3.22 (GPA1); also elsewhere on the board
P_C1: U1.3 (GPB2); also elsewhere on the board
P_C2: U1.6 (GPB5); also elsewhere on the board
P_C3: U1.28 (GPA7); also elsewhere on the board
P_C4: U1.25 (GPA4); also elsewhere on the board
P_C5: U1.22 (GPA1); also elsewhere on the board
P_C6: U2.2 (GPB1); also elsewhere on the board
P_C7: U2.5 (GPB4); also elsewhere on the board
P_C8: U2.8 (GPB7); also elsewhere on the board
P_C9: U2.26 (GPA5); also elsewhere on the board
P_C10: U2.23 (GPA2); also elsewhere on the board
P_C11: U3.1 (GPB0); also elsewhere on the board
P_C12: U3.4 (GPB3); also elsewhere on the board
P_C13: U3.7 (GPB6); also elsewhere on the board
P_C14: U3.27 (GPA6); also elsewhere on the board
P_C15: U3.24 (GPA3); also elsewhere on the board
P_C16: U3.21 (GPA0); also elsewhere on the board
SCK: U1.12 (SCK), U2.12 (SCK), U3.12 (SCK); also elsewhere on the board
VCC: U1.9, U2.9, U3.9; also elsewhere on the board
